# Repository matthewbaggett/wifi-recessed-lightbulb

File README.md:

# WifiLight MR16 Mk8

Its very easy to get hold of a wifi-controlled lightbulb that plugs into an Edison Screw (E27) fitting or a Bayonette fitting (B22).. It is possible to get some IR remote controlled GU10 light fittings.. But what about an ESP8266-powered wifi-enabled light fitting to go into an MR16 socket?

With this in mind I have set out to develop such a product.

# Programming Harness

To make it easy to program the ESP9266 via the 1.5mm JST socket, I designed a FTDI-based programmer. I have also attached a SMD 6 pin header that works just like any other FTDI serial USB device to make it useful beyond the life of this project.

# Licence

<br />This work is licensed under a <a rel="license" href="http://creativecommons.org/licenses/by-nc/4.0/">Creative Commons Attribution-NonCommercial 4.0 International License</a>.

May be re-licenced on request.

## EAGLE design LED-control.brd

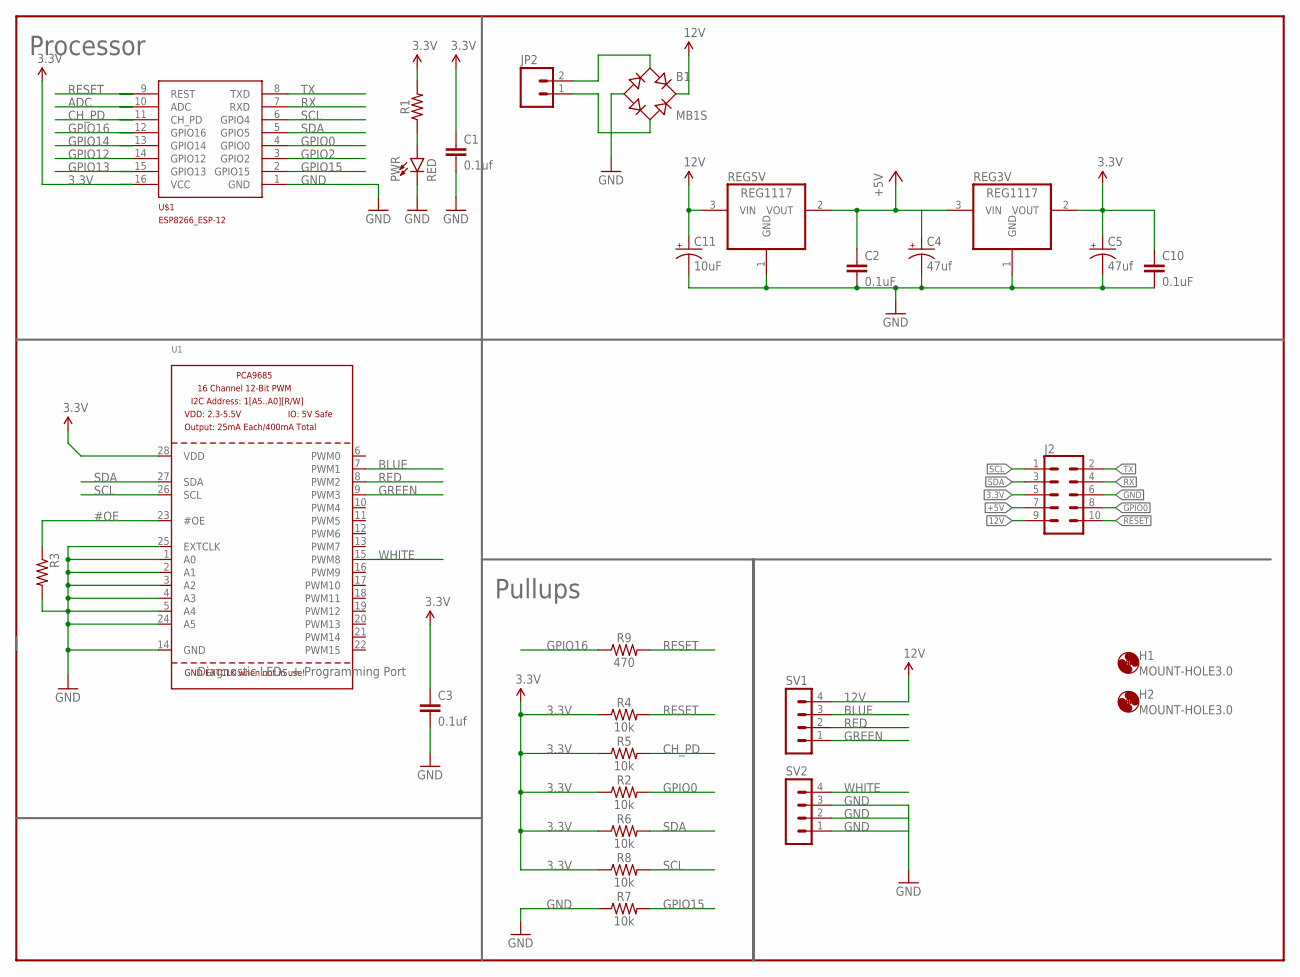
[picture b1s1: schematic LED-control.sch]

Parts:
B1: MB1S; SOIC-4
C1, C3: 0.1uf; C1206
C2, C10: 0.1uF; C1206
C4, C5: 47uf; PANASONIC_C
C11: 10uF; EIA3216
FRAME1: FRAME-LETTERNO_PACKAGE; DUMMY
H1, H2: MOUNT-HOLE3.0; 3,0
J2: CONN_05X2SHD; 2X5-SHROUDED
JP2: M02JST-PTH-VERT; JST-2-PTH-VERT
PWR: RED; LED-1206
R1: 1206
R2, R4, R5, R6, R7, R8: 10k; 1206
R3: R1206
R9: 470; 1206
REG3V, REG5V: REG1117; SOT223
SV1, SV2: MA04-1
U1: PCA9685; TSSOP28
U$1: ESP8266_ESP-12; ESP8266-ESP12

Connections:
3.3V: C1.1, C3.1, C5.+, C10.1, J2.5, R1.2, R2.1, R4.1, R5.1, R6.1, R8.1, REG3V.2 (VOUT), U1.28 (VDD), U$1.16 (VCC)
12V: B1.+, C11.A (+), J2.9, REG5V.3 (VIN), SV1.4
#OE: R3.1, U1.23 (#OE)
+5V: C2.1, C4.+, J2.7, REG3V.3 (VIN), REG5V.2 (VOUT)
ADC: U$1.10 (ADC)
BLUE: SV1.3, U1.7 (PWM1)
CH_PD: R5.2, U$1.11 (CH_PD)
GND: B1.-, C1.2, C2.2, C3.2, C4.-, C5.-, C10.2, C11.C (-), J2.6, PWR.C, R3.2, R7.1, REG3V.1 (GND), REG5V.1 (GND), SV2.1, SV2.2, SV2.3, U1.1 (A0), U1.2 (A1), U1.3 (A2), U1.4 (A3), U1.5 (A4), U1.14 (GND), U1.24 (A5), U1.25 (EXTCLK), U$1.1 (GND)
GPIO0: J2.8, R2.2, U$1.4 (GPIO0)
GPIO2: U$1.3 (GPIO2)
GPIO12: U$1.14 (GPIO12)
GPIO13: U$1.15 (GPIO13)
GPIO14: U$1.13 (GPIO14)
GPIO15: R7.2, U$1.2 (GPIO15)
GPIO16: R9.1, U$1.12 (GPIO16)
GREEN: SV1.1, U1.9 (PWM3)
unnamed: PWR.A, R1.1
unnamed: B1.~1 (AC1), JP2.2
unnamed: B1.~2 (AC2), JP2.1
RED: SV1.2, U1.8 (PWM2)
RESET: J2.10, R4.2, R9.2, U$1.9 (REST)
RX: J2.4, U$1.7 (RXD)
SCL: J2.1, R8.2, U1.26 (SCL), U$1.6 (GPIO4)
SDA: J2.3, R6.2, U1.27 (SDA), U$1.5 (GPIO5)
TX: J2.2, U$1.8 (TXD)
WHITE: SV2.4, U1.15 (PWM8)

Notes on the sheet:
Processor
Pullups
Diagnostic LEDs + Programming Port

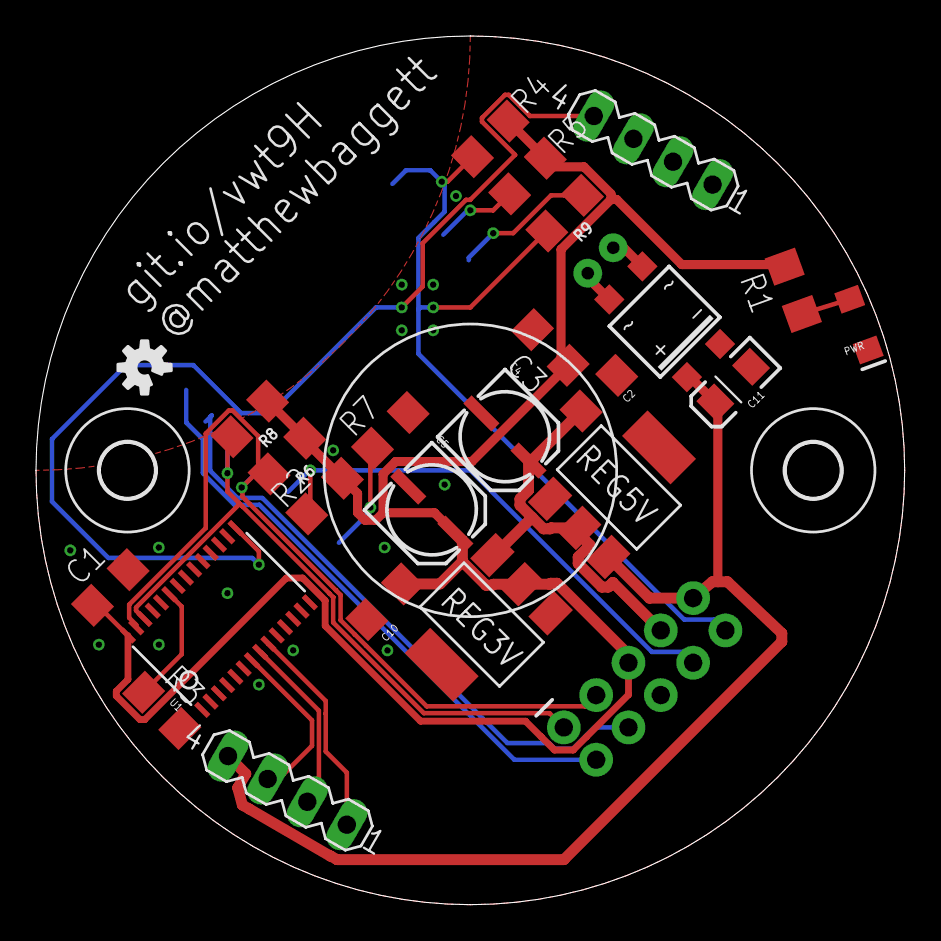
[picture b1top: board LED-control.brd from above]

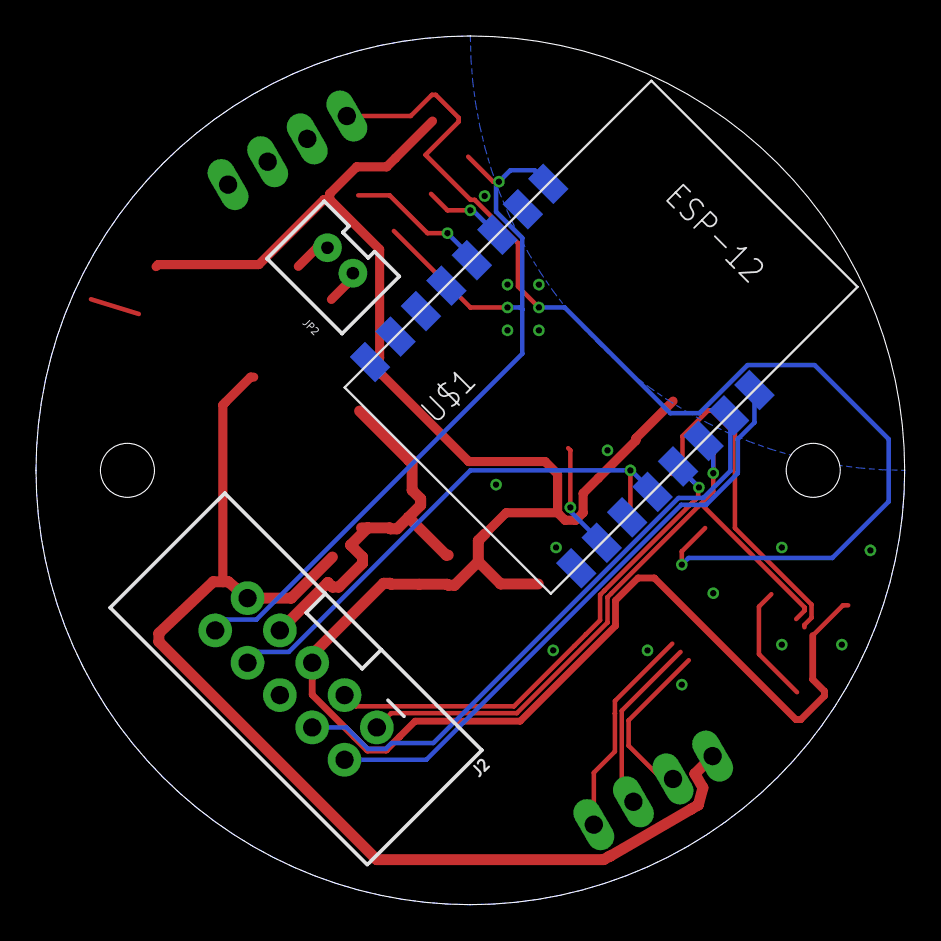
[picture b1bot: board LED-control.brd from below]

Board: 2 copper layers, 48.3 x 48.3 mm, 30 parts (3 on the bottom side), 21 nets.

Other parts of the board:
LOGO3: OSHW-LOGOS; OSHW-LOGO-S

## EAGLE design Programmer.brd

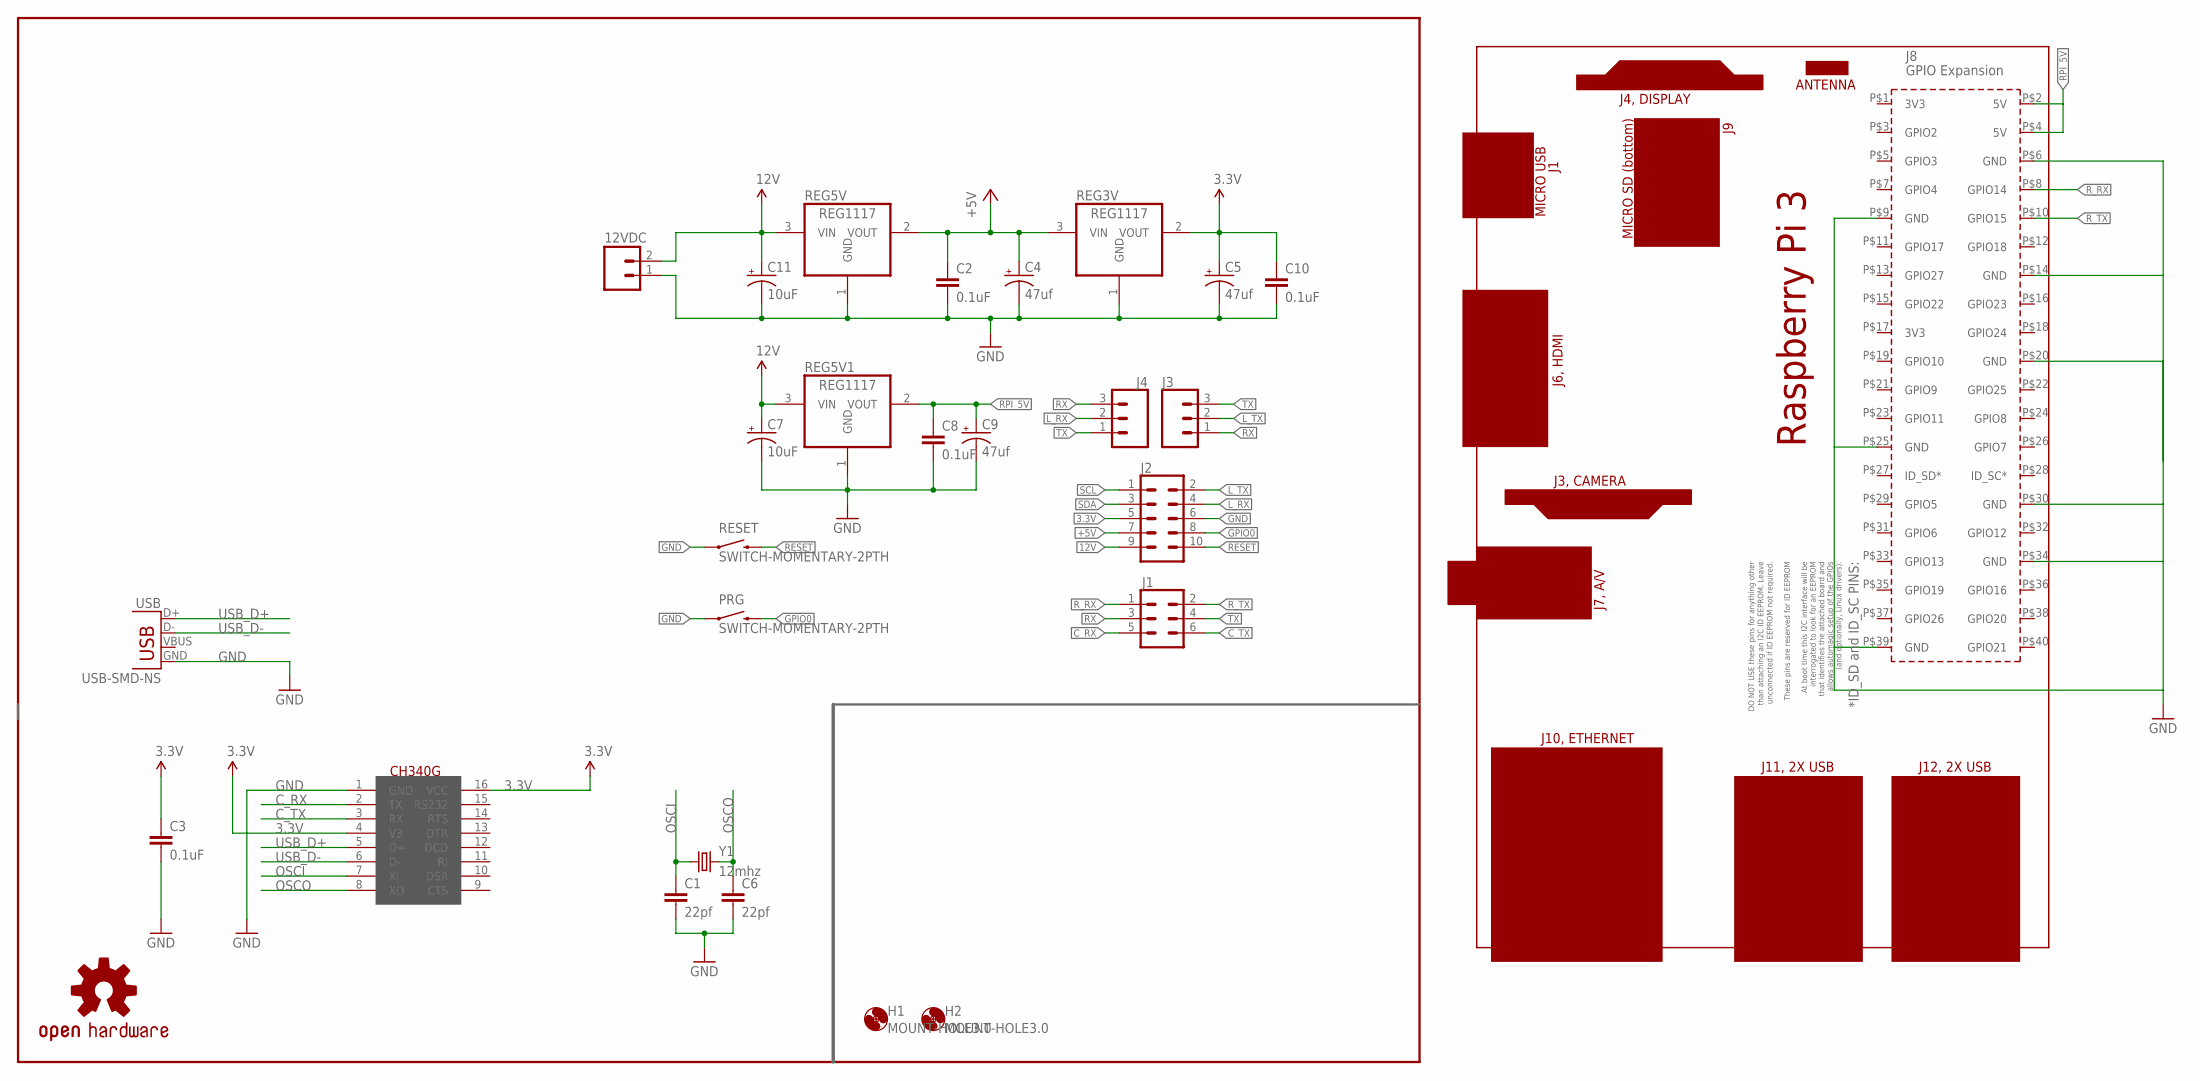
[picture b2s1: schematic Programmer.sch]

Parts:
12VDC: M023.5MM; SCREWTERMINAL-3.5MM-2
C1, C6: 22pf; 1206
C2, C8, C10: 0.1uF; 0603-CAP
C3: 0.1uF; C1206K
C4, C5, C9: 47uf; PANASONIC_C
C7, C11: 10uF; EIA3216
FRAME1: FRAME-LETTERNO_PACKAGE; DUMMY
H1, H2: MOUNT-HOLE3.0; 3,0
J1: CONN_03X22X3_SILK_MALE_PTH; 2X3
J2: CONN_05X2SHD; 2X5-SHROUDED
J3, J4: CONN_03LOCK; 1X03_LOCK
LOGO2: OSHW-LOGOS; OSHW-LOGO-S
PCB1: RPI3
PRG: SWITCH-MOMENTARY-2PTH; TACTILE-PTH
REG3V, REG5V, REG5V1: REG1117; SOT223
RESET: SWITCH-MOMENTARY-2PTH; TACTILE-PTH
U$2: CH340G; SOIC16
USB: USB-SMD-NS; USB-MINIB-NOSTOP
Y1: 12mhz; HC49UP

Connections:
3.3V: C3.1, C5.+, C10.1, J2.5, REG3V.2 (VOUT), U$2.4 (V3), U$2.16 (VCC)
12V: 12VDC.2, C7.A (+), C11.A (+), J2.9, REG5V.3 (VIN), REG5V1.3 (VIN)
+5V: C2.1, C4.+, J2.7, REG3V.3 (VIN), REG5V.2 (VOUT)
C_RX: J1.5, U$2.2 (TX)
C_TX: J1.6, U$2.3 (RX)
GND: 12VDC.1, C1.2, C2.2, C3.2, C4.-, C5.-, C6.2, C7.C (-), C8.2, C9.-, C10.2, C11.C (-), J2.6, PCB1.P$6 (GND), PCB1.P$9 (GND), PCB1.P$14 (GND), PCB1.P$20 (GND), PCB1.P$25 (GND), PCB1.P$30 (GND), PCB1.P$34 (GND), PCB1.P$39 (GND), PRG.1, REG3V.1 (GND), REG5V.1 (GND), REG5V1.1 (GND), RESET.1, U$2.1 (GND), USB.GND
GPIO0: J2.8, PRG.3 (2)
L_RX: J2.4, J4.2
L_TX: J2.2, J3.2
OSCI: C1.1, U$2.7 (XI), Y1.1
OSCO: C6.1, U$2.8 (XO), Y1.2
RESET: J2.10, RESET.3 (2)
RPI_5V: C8.1, C9.+, PCB1.P$2 (5V), PCB1.P$4 (5V), REG5V1.2 (VOUT)
RX: J1.3, J3.1, J4.3
R_RX: J1.1, PCB1.P$8 (GPIO14)
R_TX: J1.2, PCB1.P$10 (GPIO15)
SCL: J2.1
SDA: J2.3
TX: J1.4, J3.3, J4.1
USB_D+: U$2.5 (D+), USB.D+
USB_D-: U$2.6 (D-), USB.D-

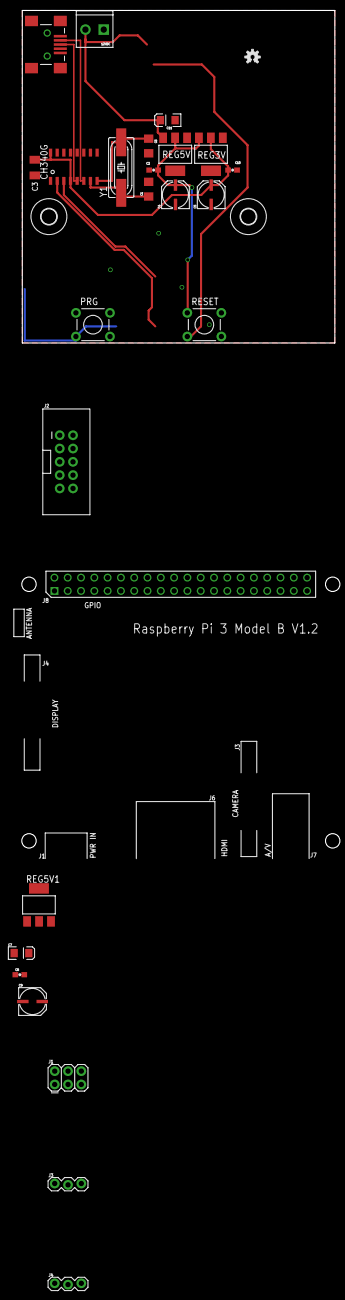
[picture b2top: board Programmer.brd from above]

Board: 2 copper layers, 59.7 x 63.5 mm, 29 parts (0 on the bottom side), 19 nets.

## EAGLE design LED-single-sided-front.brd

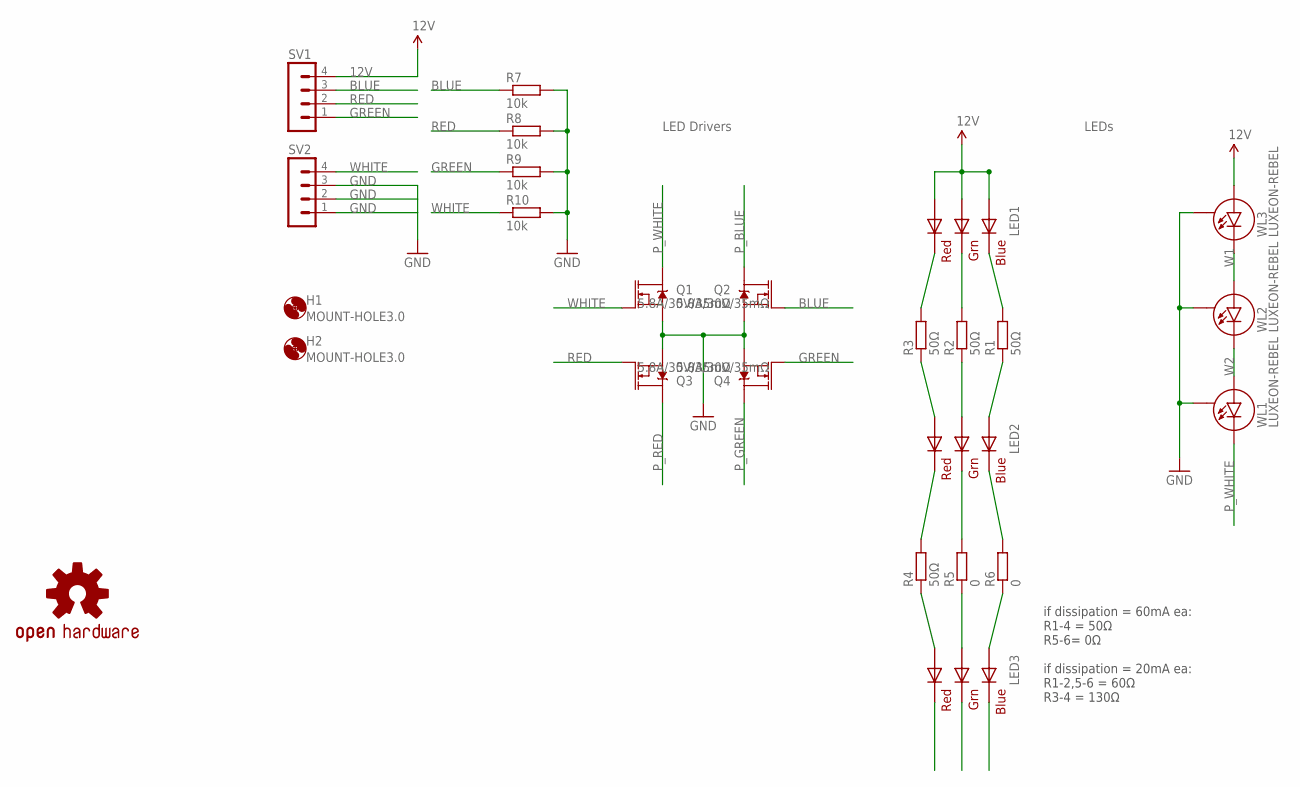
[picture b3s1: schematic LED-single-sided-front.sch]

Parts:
H1, H2: MOUNT-HOLE3.0; 3,0
LED1, LED2, LED3: RGBLED5050
LOGO1: OSHW-LOGOS; OSHW-LOGO-S
Q1, Q2, Q3, Q4: 5.8A/30V/35mΩ; SOT23-3
R1, R2, R3, R4: 50Ω; R1206
R5, R6: 0; R1206
R7, R8, R9, R10: 10k; R1206
SV1, SV2: MA04-1
WL1, WL2, WL3: LUXEON-REBEL

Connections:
12V: LED1.1 (GREEN_A), LED1.2 (RED_A), LED1.3 (BLUE_A), SV1.4, WL3.ANODE (A)
BLUE: Q2.1 (G), R7.1, SV1.3
GND: Q1.2 (S), Q2.2 (S), Q3.2 (S), Q4.2 (S), R7.2, R8.2, R9.2, R10.2, SV2.1, SV2.2, SV2.3, WL1.P$3 (S), WL2.P$3 (S), WL3.P$3 (S)
GREEN: Q4.1 (G), R9.1, SV1.1
unnamed: LED1.5 (RED_C), R3.2
unnamed: LED1.6 (GREEN_C), R2.2
unnamed: LED1.4 (BLUE_C), R1.2
unnamed: LED3.2 (RED_A), R4.1
unnamed: LED3.1 (GREEN_A), R5.1
unnamed: LED3.3 (BLUE_A), R6.1
unnamed: LED2.5 (RED_C), R4.2
unnamed: LED2.6 (GREEN_C), R5.2
unnamed: LED2.4 (BLUE_C), R6.2
unnamed: LED2.2 (RED_A), R3.1
unnamed: LED2.1 (GREEN_A), R2.1
unnamed: LED2.3 (BLUE_A), R1.1
P_BLUE: LED3.4 (BLUE_C), Q2.3 (D)
P_GREEN: LED3.6 (GREEN_C), Q4.3 (D)
P_RED: LED3.5 (RED_C), Q3.3 (D)
P_WHITE: Q1.3 (D), WL1.CATHODE (C)
RED: Q3.1 (G), R8.1, SV1.2
W1: WL2.ANODE (A), WL3.CATHODE (C)
W2: WL1.ANODE (A), WL2.CATHODE (C)
WHITE: Q1.1 (G), R10.1, SV2.4

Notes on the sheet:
LEDs
LED Drivers
if dissipation = 60mA ea: R1-4 = 50Ω R5-6= 0Ω if dissipation = 20mA ea: R1-2,5-6 = 60Ω R3-4 = 130Ω

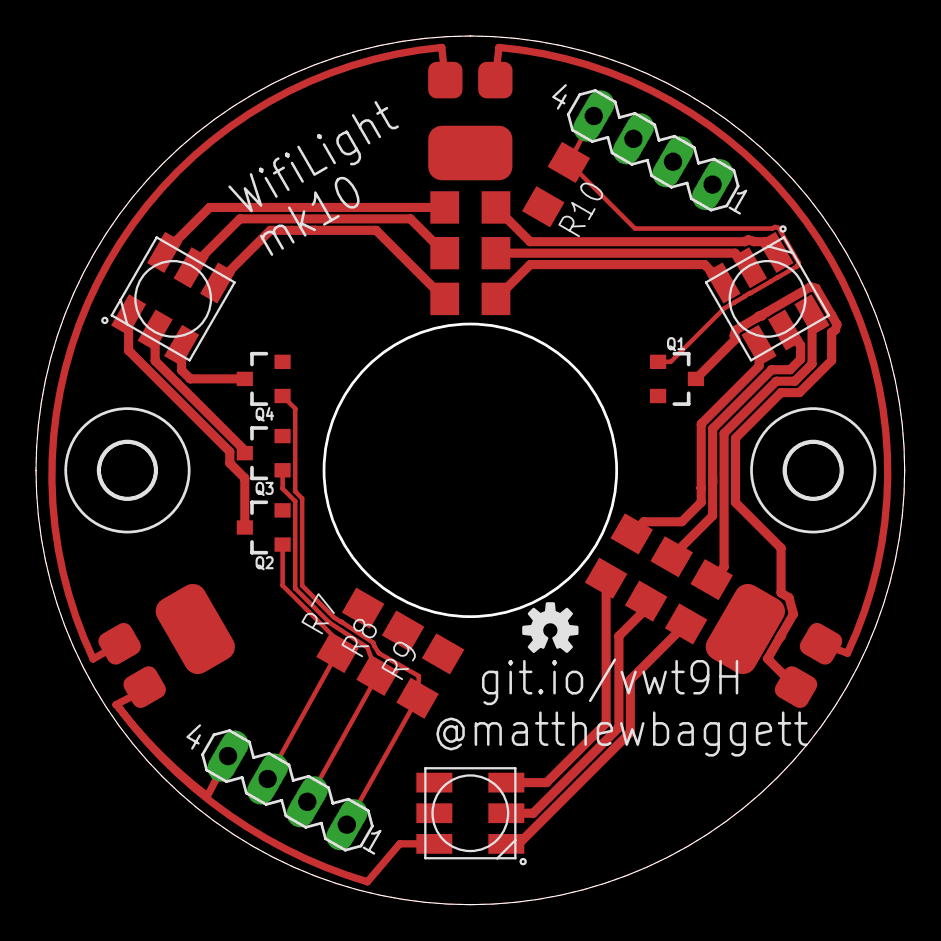
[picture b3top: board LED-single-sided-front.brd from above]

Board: 2 copper layers, 48.3 x 48.3 mm, 25 parts (0 on the bottom side), 24 nets.

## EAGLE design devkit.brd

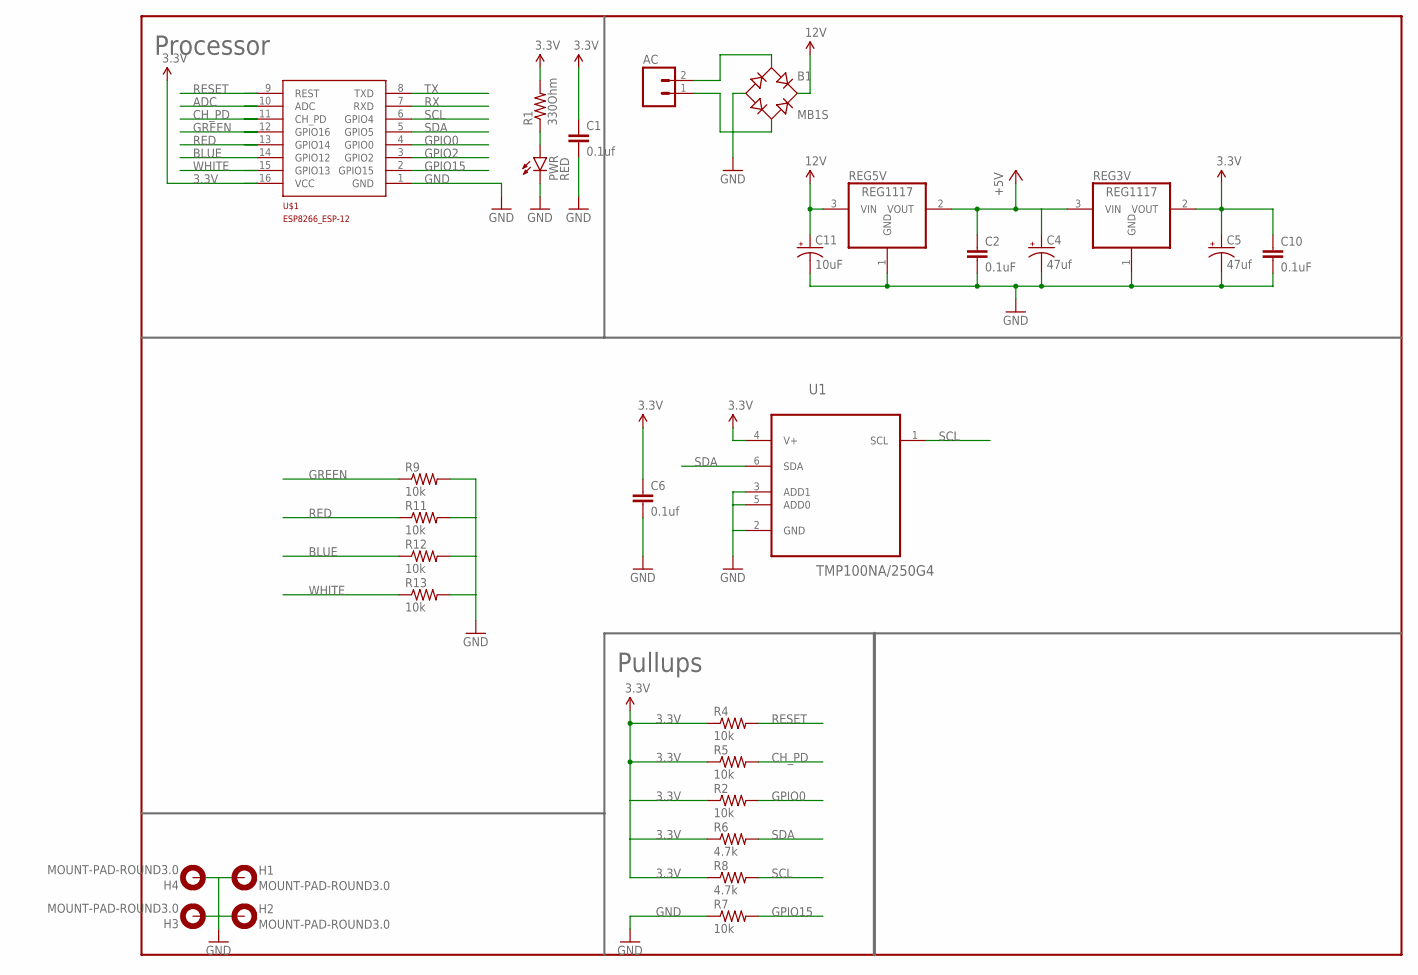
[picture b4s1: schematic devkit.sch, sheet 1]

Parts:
AC: M02JST-PTH-VERT; JST-2-PTH-VERT
B1: MB1S; SOIC-4
C1, C6: 0.1uf; 0805
C2, C10: 0.1uF; 0805
C4, C5: 47uf; PANASONIC_C
C11: 10uF; EIA3216
FRAME1: FRAME-LETTERNO_PACKAGE; DUMMY
H1, H2, H3, H4: MOUNT-PAD-ROUND3.0; 3,0-PAD
PWR: RED; LED-1206
R1: 330Ohm; 0805
R2, R4, R5, R7, R9, R11, R12, R13: 10k; 0805
R6, R8: 4.7k; 0805
REG3V, REG5V: REG1117; SOT223
U1: TMP100NA/250G4; SOT95P280X145-6N
U$1: ESP8266_ESP-12; ESP8266-ESP12

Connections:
3.3V: C1.1, C5.+, C6.1, C10.1, R1.2, R2.1, R4.1, R5.1, R6.1, R8.1, REG3V.2 (VOUT), U1.4 (V+), U$1.16 (VCC); also elsewhere on the board
12V: B1.+, C11.A (+), REG5V.3 (VIN); also elsewhere on the board
+5V: C2.1, C4.+, REG3V.3 (VIN), REG5V.2 (VOUT); also elsewhere on the board
ADC: U$1.10 (ADC)
BLUE: R12.1, U$1.14 (GPIO12); also elsewhere on the board
CH_PD: R5.2, U$1.11 (CH_PD)
GND: B1.-, C1.2, C2.2, C4.-, C5.-, C6.2, C10.2, C11.C (-), H1.B3,0, H2.B3,0, H3.B3,0, H4.B3,0, PWR.C, R7.1, R9.2, R11.2, R12.2, R13.2, REG3V.1 (GND), REG5V.1 (GND), U1.2 (GND), U1.3 (ADD1), U1.5 (ADD0), U$1.1 (GND); also elsewhere on the board
GPIO0: R2.2, U$1.4 (GPIO0); also elsewhere on the board
GPIO2: U$1.3 (GPIO2)
GPIO15: R7.2, U$1.2 (GPIO15)
GREEN: R9.1, U$1.12 (GPIO16); also elsewhere on the board
unnamed: PWR.A, R1.1
unnamed: AC.2, B1.~1 (AC1)
unnamed: AC.1, B1.~2 (AC2)
RED: R11.1, U$1.13 (GPIO14); also elsewhere on the board
RESET: R4.2, U$1.9 (REST); also elsewhere on the board
RX: U$1.7 (RXD); also elsewhere on the board
SCL: R8.2, U1.1 (SCL), U$1.6 (GPIO4)
SDA: R6.2, U1.6 (SDA), U$1.5 (GPIO5)
TX: U$1.8 (TXD); also elsewhere on the board
WHITE: R13.1, U$1.15 (GPIO13); also elsewhere on the board

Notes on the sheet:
Processor
Pullups

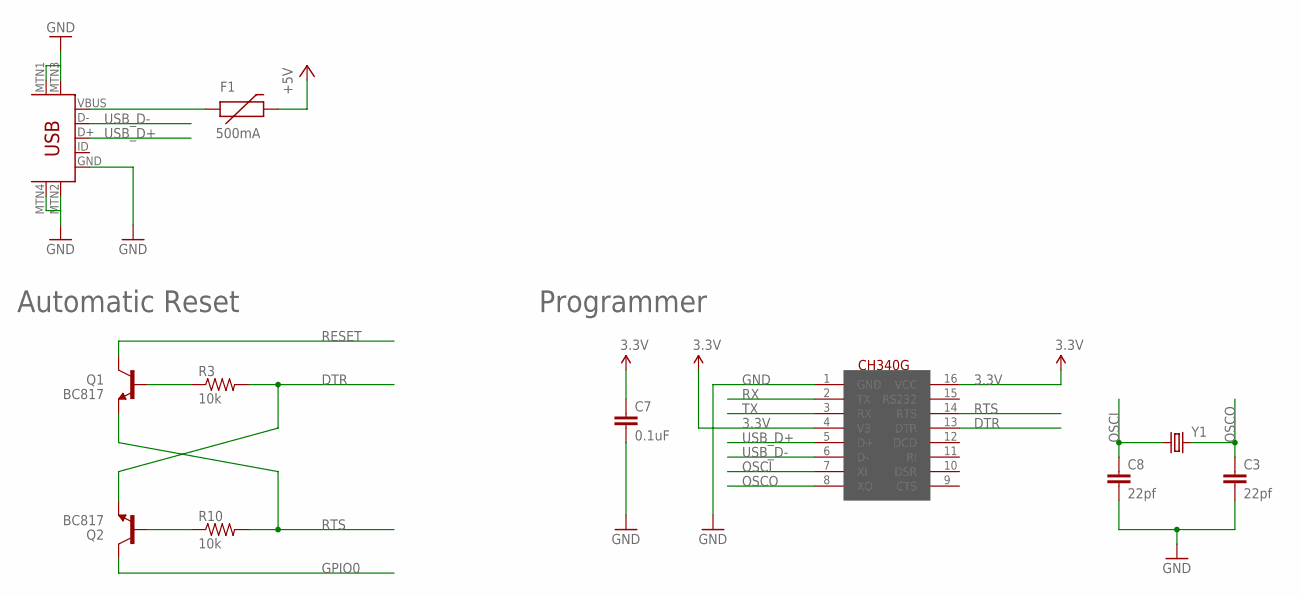
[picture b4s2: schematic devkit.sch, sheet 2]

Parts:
C3, C8: 22pf; 0805
C7: 0.1uF; 0805
F1: 500mA; PTC-1206-WIDE
Q1, Q2: BC817; SOT23-3
R3, R10: 10k; 0805
U$2: CH340G; SOIC16
U$3: USB-MINIB-5PIN; USB-MINIB
Y1: CRYSTALSMD; HC49UP

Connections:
3.3V: C7.1, U$2.4 (V3), U$2.16 (VCC); also elsewhere on the board
+5V: F1.2; also elsewhere on the board
DTR: Q2.2 (E), R3.2, U$2.13 (DTR)
GND: C3.2, C7.2, C8.2, U$2.1 (GND), U$3.GND, U$3.MTN1 (MTN2), U$3.MTN2 (MTN3), U$3.MTN3 (MTN1), U$3.MTN4; also elsewhere on the board
GPIO0: Q2.3 (C); also elsewhere on the board
unnamed: Q1.1 (B), R3.1
unnamed: Q2.1 (B), R10.1
unnamed: F1.1, U$3.VBUS
OSCI: C8.1, U$2.7 (XI), Y1.1
OSCO: C3.1, U$2.8 (XO), Y1.2
RESET: Q1.3 (C); also elsewhere on the board
RTS: Q1.2 (E), R10.2, U$2.14 (RTS)
RX: U$2.2 (TX); also elsewhere on the board
TX: U$2.3 (RX); also elsewhere on the board
USB_D+: U$2.5 (D+), U$3.D+
USB_D-: U$2.6 (D-), U$3.D-

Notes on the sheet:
Programmer
Automatic Reset

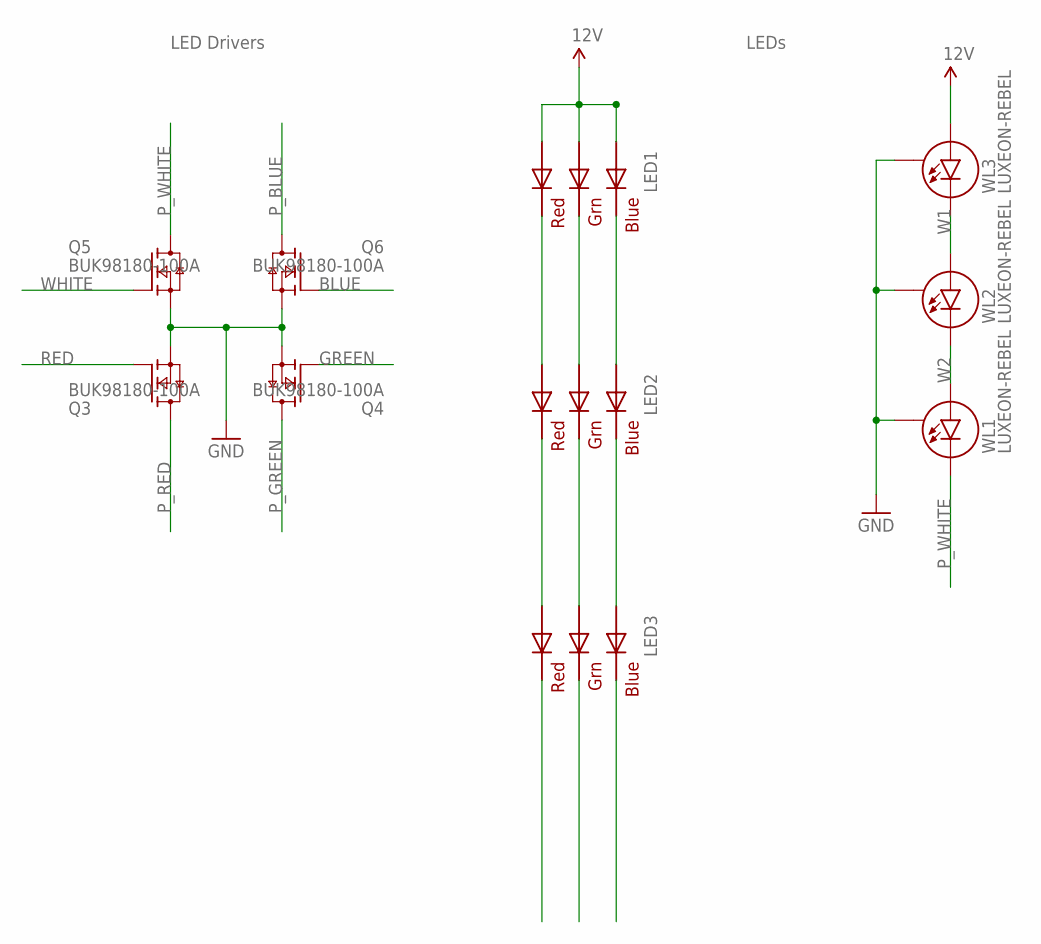
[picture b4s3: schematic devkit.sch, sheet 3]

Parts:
LED1, LED2, LED3: RGBLED5050
Q3, Q4, Q5, Q6: BUK98180-100A; SOT223
WL1, WL2, WL3: LUXEON-REBEL

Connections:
12V: LED1.1 (GREEN_A), LED1.2 (RED_A), LED1.3 (BLUE_A), WL3.ANODE (A); also elsewhere on the board
BLUE: Q6.1 (G); also elsewhere on the board
GND: Q3.3 (S), Q4.3 (S), Q5.3 (S), Q6.3 (S), WL1.P$3 (S), WL2.P$3 (S), WL3.P$3 (S); also elsewhere on the board
GREEN: Q4.1 (G); also elsewhere on the board
unnamed: LED1.6 (GREEN_C), LED2.1 (GREEN_A)
unnamed: LED1.4 (BLUE_C), LED2.3 (BLUE_A)
unnamed: LED1.5 (RED_C), LED2.2 (RED_A)
unnamed: LED2.6 (GREEN_C), LED3.1 (GREEN_A)
unnamed: LED2.4 (BLUE_C), LED3.3 (BLUE_A)
unnamed: LED2.5 (RED_C), LED3.2 (RED_A)
P_BLUE: LED3.4 (BLUE_C), Q6.2 (D), Q6.4 (D)
P_GREEN: LED3.6 (GREEN_C), Q4.2 (D), Q4.4 (D)
P_RED: LED3.5 (RED_C), Q3.2 (D), Q3.4 (D)
P_WHITE: Q5.2 (D), Q5.4 (D), WL1.CATHODE (C)
RED: Q3.1 (G); also elsewhere on the board
W1: WL2.ANODE (A), WL3.CATHODE (C)
W2: WL1.ANODE (A), WL2.CATHODE (C)
WHITE: Q5.1 (G); also elsewhere on the board

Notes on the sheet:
LEDs
LED Drivers

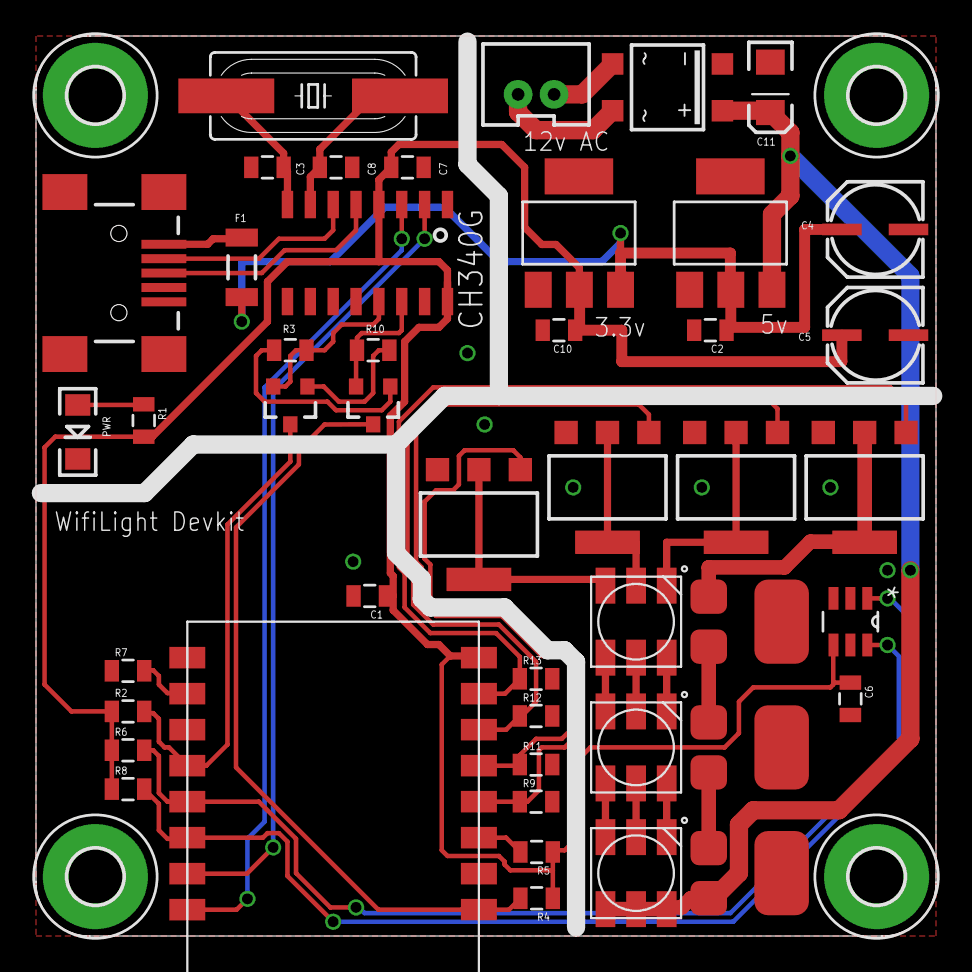
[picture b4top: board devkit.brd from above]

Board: 2 copper layers, 50.0 x 50.0 mm, 51 parts (0 on the bottom side), 40 nets.

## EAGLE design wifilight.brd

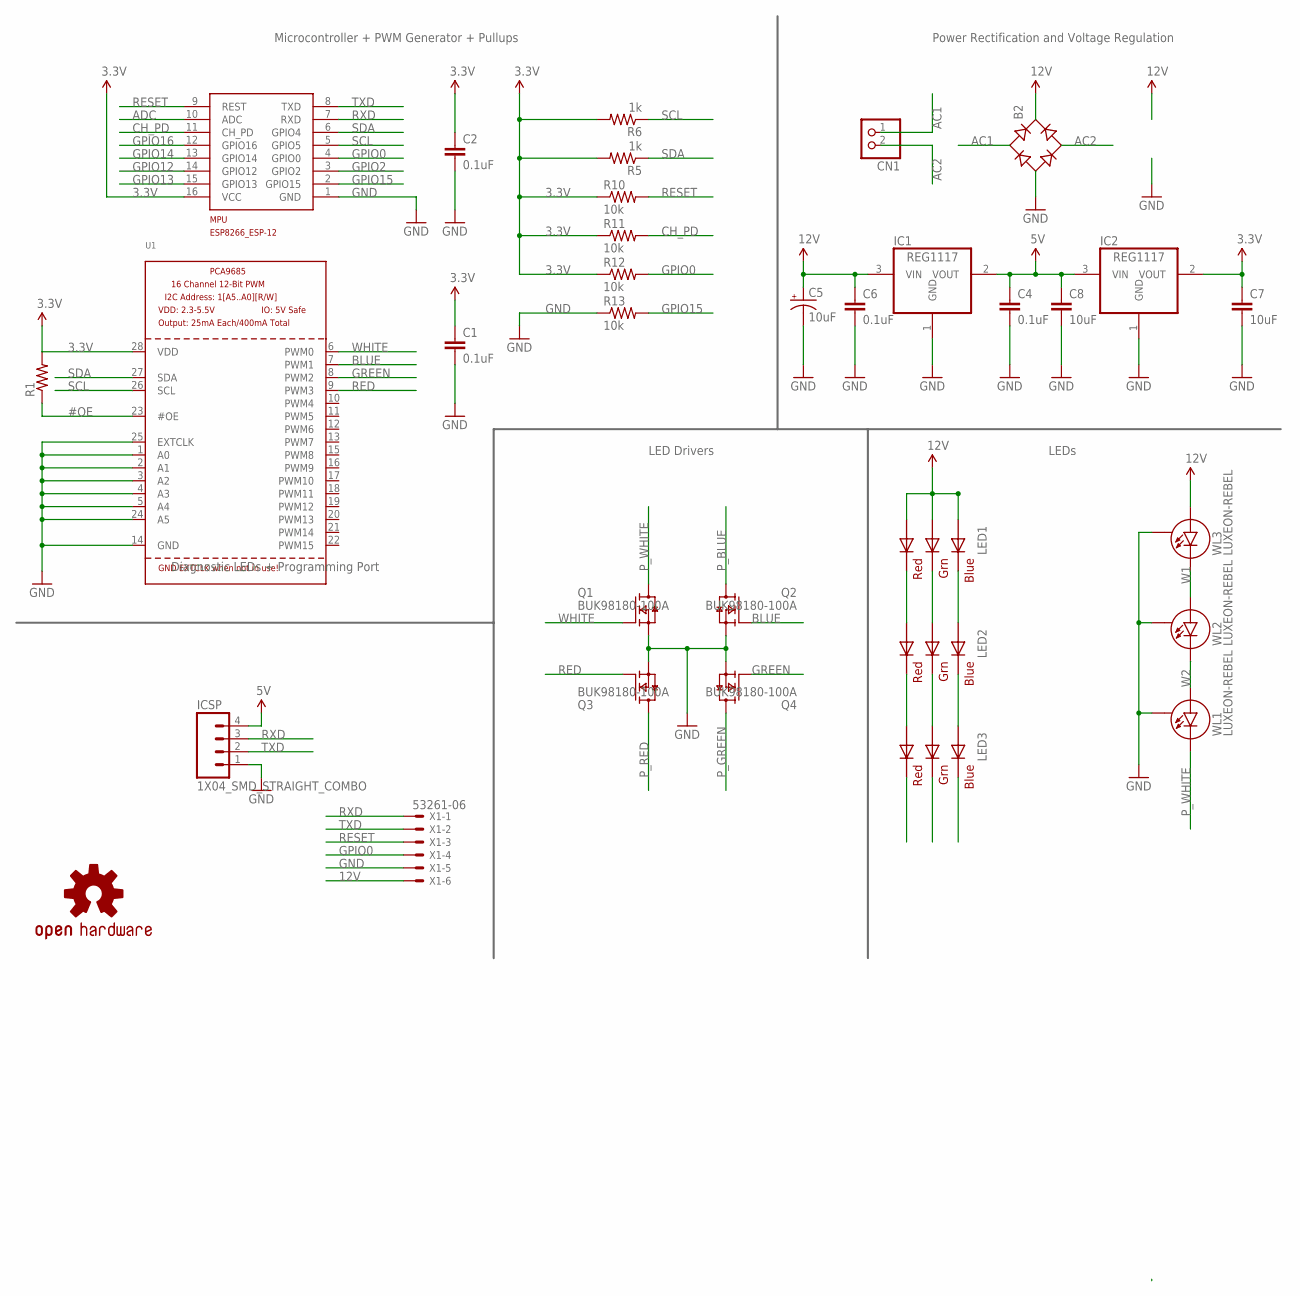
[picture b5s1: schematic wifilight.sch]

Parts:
B2: DBLS203G; DBS
C1, C2, C4, C6: 0.1uF; 1206
C5: 10uF; EIA3216
C7, C8: 10uF; 1206
CN1: JST_2PIN-THM; JST-PH-2-THM
IC1, IC2: REG1117; SOT223
ICSP: 1X04_SMD_STRAIGHT_COMBO
LED1, LED2, LED3: RGBLED5050
LOGO1: OSHW-LOGOS; OSHW-LOGO-S
MPU: ESP8266_ESP-12; ESP8266-ESP12
Q1, Q2, Q3, Q4: BUK98180-100A; SOT223
R1: RESISTOR1206; 1206
R5, R6: 1k; 1206
R10, R11, R12, R13: 10k; 1206
U1: PCA9685; TSSOP28
WL1, WL2, WL3: LUXEON-REBEL
X1: 53261-06

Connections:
3.3V: C1.1, C2.1, C7.1, IC2.2 (VOUT), MPU.16 (VCC), R1.2, R5.2, R6.2, R10.1, R11.1, R12.1, U1.28 (VDD)
5V: C4.1, C8.1, IC1.2 (VOUT), IC2.3 (VIN), ICSP.4
12V: B2.+, C5.A (+), C6.1, IC1.3 (VIN), LED1.1 (GREEN_A), LED1.2 (RED_A), LED1.3 (BLUE_A), WL3.ANODE (A), X1.6
#OE: R1.1, U1.23 (#OE)
AC1: B2.AC1, CN1.1 (2)
AC2: B2.AC2, CN1.2 (1)
ADC: MPU.10 (ADC)
BLUE: Q2.1 (G), U1.7 (PWM1)
CH_PD: MPU.11 (CH_PD), R11.2
GND: B2.-, C1.2, C2.2, C4.2, C5.C (-), C6.2, C7.2, C8.2, IC1.1 (GND), IC2.1 (GND), ICSP.1, MPU.1 (GND), Q1.3 (S), Q2.3 (S), Q3.3 (S), Q4.3 (S), R13.1, U1.1 (A0), U1.2 (A1), U1.3 (A2), U1.4 (A3), U1.5 (A4), U1.14 (GND), U1.24 (A5), U1.25 (EXTCLK), WL1.P$3 (S), WL2.P$3 (S), WL3.P$3 (S), X1.5
GPIO0: MPU.4 (GPIO0), R12.2, X1.4
GPIO2: MPU.3 (GPIO2)
GPIO12: MPU.14 (GPIO12)
GPIO13: MPU.15 (GPIO13)
GPIO14: MPU.13 (GPIO14)
GPIO15: MPU.2 (GPIO15), R13.2
GPIO16: MPU.12 (GPIO16)
GREEN: Q4.1 (G), U1.8 (PWM2)
unnamed: LED2.5 (RED_C), LED3.2 (RED_A)
unnamed: LED2.6 (GREEN_C), LED3.1 (GREEN_A)
unnamed: LED2.4 (BLUE_C), LED3.3 (BLUE_A)
unnamed: LED1.5 (RED_C), LED2.2 (RED_A)
unnamed: LED1.6 (GREEN_C), LED2.1 (GREEN_A)
unnamed: LED1.4 (BLUE_C), LED2.3 (BLUE_A)
P_BLUE: LED3.4 (BLUE_C), Q2.2 (D), Q2.4 (D)
P_GREEN: LED3.6 (GREEN_C), Q4.2 (D), Q4.4 (D)
P_RED: LED3.5 (RED_C), Q3.2 (D), Q3.4 (D)
P_WHITE: Q1.2 (D), Q1.4 (D), WL1.CATHODE (C)
RED: Q3.1 (G), U1.9 (PWM3)
RESET: MPU.9 (REST), R10.2, X1.3
RXD: ICSP.3, MPU.7 (RXD), X1.1
SCL: MPU.5 (GPIO5), R6.1, U1.26 (SCL)
SDA: MPU.6 (GPIO4), R5.1, U1.27 (SDA)
TXD: ICSP.2, MPU.8 (TXD), X1.2
W1: WL2.ANODE (A), WL3.CATHODE (C)
W2: WL1.ANODE (A), WL2.CATHODE (C)
WHITE: Q1.1 (G), U1.6 (PWM0)

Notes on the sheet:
Microcontroller + PWM Generator + Pullups
Power Rectification and Voltage Regulation
LEDs
LED Drivers
Diagnostic LEDs + Programming Port

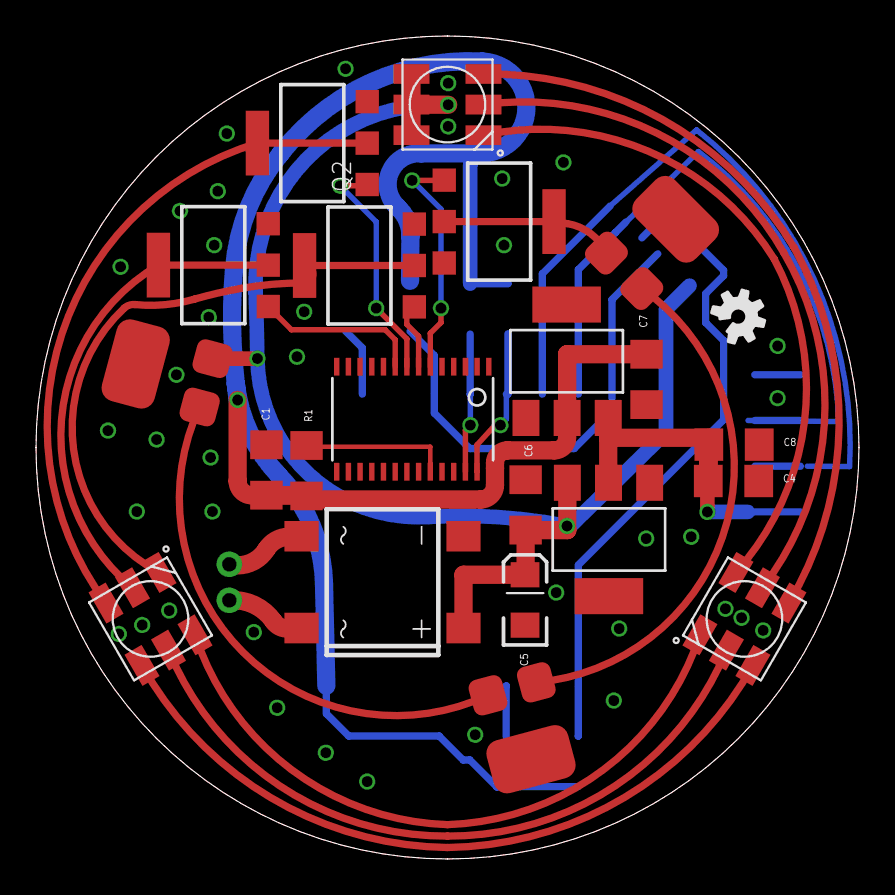
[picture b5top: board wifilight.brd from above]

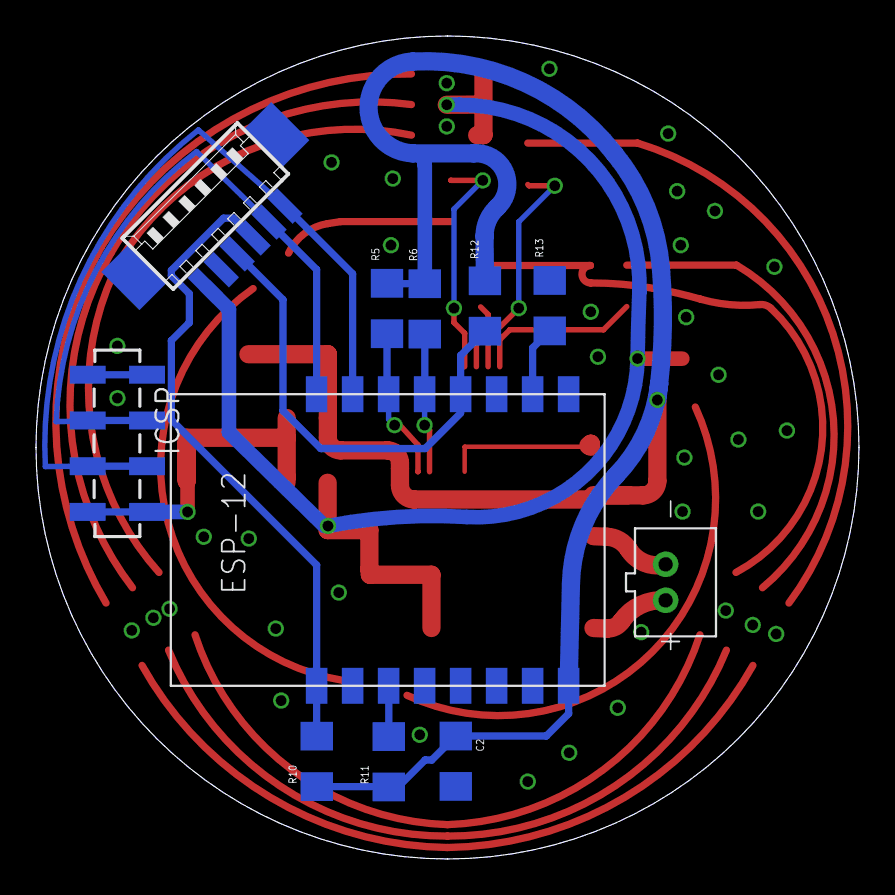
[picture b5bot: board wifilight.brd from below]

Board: 2 copper layers, 45.7 x 45.7 mm, 33 parts (11 on the bottom side), 31 nets.

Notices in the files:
parts and their libraries:
SparkFun-Aesthetics: Licensing: Creative Commons ShareAlike 4.0 International - https://creativecommons.org/licenses/by-sa/4.0
SparkFun-Aesthetics: Released under the Creative Commons Attribution Share-Alike 4.0 License
SparkFun-Aesthetics: https://creativecommons.org/licenses/by-sa/4.0
